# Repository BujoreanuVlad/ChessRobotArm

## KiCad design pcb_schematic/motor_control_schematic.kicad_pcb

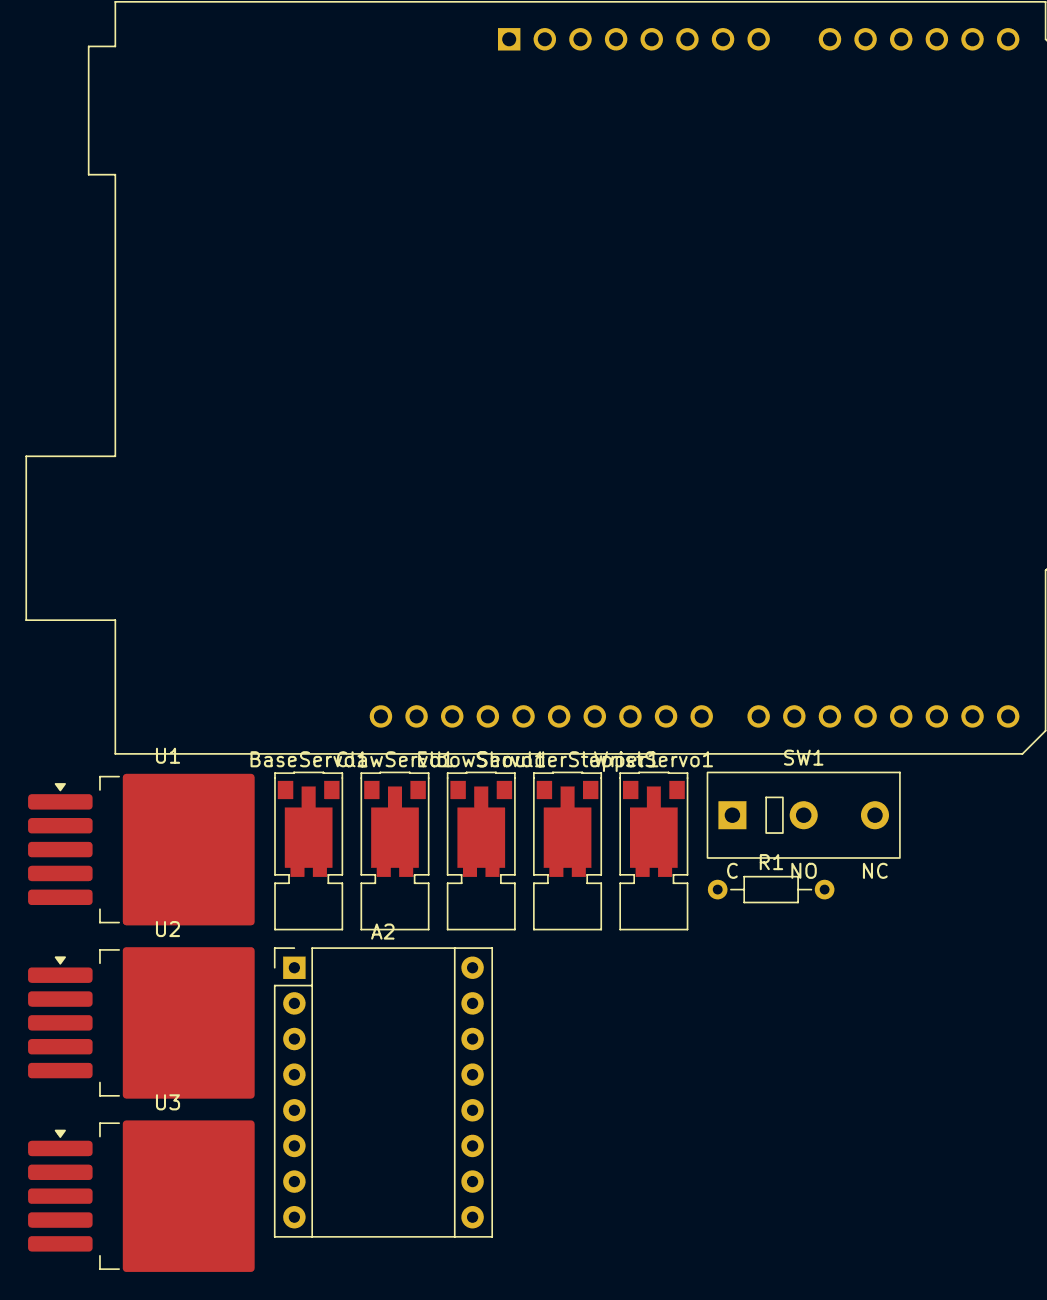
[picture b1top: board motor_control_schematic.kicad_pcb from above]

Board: 2 copper layers, 12 parts (0 on the bottom side), 15 nets, no tracks yet.

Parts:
A1: Arduino_UNO_R3
A2: Pololu_Breakout_DRV8825; Pololu_Breakout-16_15.2x20.3mm
BaseServo1: Motor_Servo; Vybronics_VZ30C1T8219732L
ClawServo1: Motor_Servo; Vybronics_VZ30C1T8219732L
ElbowServo1: Motor_Servo; Vybronics_VZ30C1T8219732L
R1: 10K; R_Axial_DIN0204_L3.6mm_D1.6mm_P7.62mm_Horizontal
SW1: SW_Push; SW_XKB_DM1-16UP-1
ShoulderStepper1: Stepper_Motor_bipolar; Vybronics_VZ30C1T8219732L
U1: XL4015; TO-263-5_TabPin3
U2, U3: LM2596S-ADJ; TO-263-5_TabPin3
WristServo1: Motor_Servo; Vybronics_VZ30C1T8219732L

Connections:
+12V: A2.8 (VMOT), U1.5 (VIN), U3.1 (VIN)
GND1: A2.7 (GND), U1.1 (GND), U2.3 (GND), U3.3 (GND)
unnamed: A1.5 (+5V), A2.13 (~RST), A2.14 (~SLP), SW1.1
unnamed: A1.17 (D2), A2.16 (DIR)
unnamed: A1.18 (D3), A2.15 (STEP)
unnamed: A1.19 (D4), R1.2, SW1.2
unnamed: A1.20 (D5), ClawServo1.1 (PWM)
unnamed: A1.21 (D6), WristServo1.1 (PWM)
unnamed: A1.24 (D9), ElbowServo1.1 (PWM)
unnamed: A1.25 (D10), BaseServo1.1 (PWM)
unnamed: A1.6 (GND), A2.1 (GND), R1.1
unnamed: A2.4 (A1), ShoulderStepper1.2 (-)
unnamed: A2.3 (A2), ShoulderStepper1.1
unnamed: BaseServo1.2 (+), ClawServo1.2 (+), U3.2 (OUT), WristServo1.2 (+)
unnamed: ElbowServo1.2 (+), U1.3 (SW), U2.1 (VIN)

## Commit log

2023-11-18 First prototype
2023-11-20 Added inertia
2023-12-22 Added a launch file and modified values to be more realistic
2024-02-09 Previous meshes for the robot
2024-02-10 First version of the stepper holder
2024-02-10 Added hole in the center for axle and fixed dimensions
2024-02-10 Fixed some distances
    Distance of the screws used to fix stepper in place shouldn't take into account the extra 5% padding of the piece
2024-02-12 Gear mounted on stepper
    Gear with a hole for the screw to better fix the gear to the stepper shaft
2024-02-14 Updated for 17HS13-0404S-PG27 motor
2024-02-14 Changes made for the 17HS13-0404S-PG27 motor
2024-02-14 Added adjustment due to difference between cylinder and base widths
2024-02-15 Shaft hole should be displaced by 1/2 of the difference, not by the whole difference
2024-02-16 22 teeth instead of 24
2024-02-17 Adapted holder for new motor
2024-02-17 First version of base gear
2024-02-17 Adjusted measurements
2024-02-17 Made gear bigger
2024-02-17 Fixed distances
2024-02-20 Made piece thicker so it opaque
2024-02-21 Tried with a smaller gear for greater torque
2024-02-21 Made gear bigger for greater torque
2024-02-23 Added gitignore
2024-02-26 First version of the first part of the arm
2024-03-02 Adjusted screw positions for part1 and built the link
2024-03-04 Finished part2 and combined link and part1
2024-03-05 Final version
2024-03-05 Increased height for part1 to compensate for link height
2024-03-05 Modified arm1 with sizes needed for arm2
2024-03-08 Added a hole for the nut
2024-03-08 Started working on board detection program
2024-03-10 Modified screw positions in part2
2024-03-24 First version of the poly gripper
2024-03-24 Padding for the current camera
2024-07-14 Sketch version of the code
2024-07-26 I forgor
2024-09-04 Made arm2 (forearm) smaller and lighter
2024-09-04 Python code to move arm through arduino
2024-09-20 Temp work
2024-10-20 Modified claw to be lighter
2024-10-20 Added project related datasheets
2024-10-20 Added documentation related files
2024-10-20 Added delay when moving servos
2024-11-02 Added variable to control servo speed
2024-11-03 Added support for shoulder control
2024-11-16 Made claws lighter
2024-11-22 Initial work
2024-12-13 Created round cut
2024-12-15 Finished clippers for holder and created servo gear
2024-12-20 Changed no of gear teeth to 33
2024-12-20 Started making changes for new arm combination
2024-12-27 Added holes to servo holder
2024-12-27 Re-made arm2 part1 design to function being turned by a gear
2024-12-27 Changed arm1 part2 design to be compatible with the new FT5335M servo
2024-12-31 Changed arm1-part2 for the 3 gear system
    The system currently uses an axle with 2 holes in it in order to secure the middle gear. This setup however snaps under the load of arm2 because of the weaknesses introduced by the holes
2024-12-31 Changed part2 to be compatible with new gear system
2024-12-31 Created axle holder
2025-01-10 Changed axle supporting gears
2025-01-10 Made servo holder thicker to not bend as much
2025-01-10 Changed arm1 to be compatible with the servo holder
2025-01-10 Added datasheet for elbow servo
2025-03-07 Modified arm1 part2 gear holes for new steel axles
2025-03-24 Changes for using a fixing screw for the servo
2025-03-25 Changed arm2-part1 to allow for more rotation freedom
2025-03-25 Made axle support thicker for arm1-part2
2025-03-26 Added code to update current shoulder angle position
2025-03-26 Made gripper holes larger to prevent the piece from breaking
2025-04-01 Fixed stepper controller
2025-04-01 Changed arm2-part1 to allow for more turning
2025-04-04 Refactored variables to use less space (converted them to 'byte' type) and wrote the function for inverse kinematics
2025-04-04 Created file for robot box
2025-04-04 Added function to convert angles to coords (forward kinematics), function to move robot vertically and added support for base servo motor
2025-04-18 Added more room for fitting on the robot
2025-04-18 Added holes for bottom panel nuts and power supply separator
2025-04-20 Finished robot box
2025-04-20 Created schematic file and added LEDs
2025-04-28 Changed servo speed and base motor lower and upper pulse width
2025-04-28 Made button holes larger and corrected switch position
2025-04-30 Renamed pcb_schematic to raspberry_schematic and created new schematic file for arduino and motor control
2025-05-01 Updated stl file
2025-05-01 Finished arduino motor controller schematic
2025-05-04 Added stepper calibration code
2025-05-05 Added vertical movement command
2025-05-06 Added horizontal movement command
2025-05-06 Added board movement command
2025-05-06 Finished raspberry schematic
2025-05-07 Created abstract Player class
2025-05-07 Changed raspberry schematic to use currently available resistors
2025-05-11 Found 2 more 15 ohm resistors to use instead of 2 10 ohm resistors
2025-05-11 Repaired mistaken gnd connection
2025-05-12 Robot state draft
2025-05-15 Added option to set LEDs in robotState
2025-05-15 Added arduino controller on raspberry side
2025-05-15 Added board move functionality in arduino
2025-05-16 Added function to get current state of led in robotState
2025-05-16 Added more base robot functions in main
2025-05-16 Fixed bugs in robotState
2025-05-16 Changed delay in arduino calibrate function
2025-05-16 Chadrv8825.h import in arduino sketch
2025-05-16 Changed main.py to contain hardcoded values for a chessboard
2025-05-16 Changed move horizontal arduino function
2025-05-16 Fixed arduino horizontal movement angle calculation
2025-05-18 More bug fixes for arduino horizontal movement
2025-05-19 Solved issue with too small buffer
2025-06-02 Fixed some bugs in horizontal movement and makeMove
2025-06-02 Changed default position of robot
2025-06-02 Fixed char to byte conversion bug
2025-06-02 Adder wrist error correction to moveVertical function
2025-06-02 Updated wrist error correction
2025-06-02 Updated wrist error correction to 15 deg
2025-06-02 Added new claw rest position
2025-06-02 Changed claw angles
2025-06-02 Switch move horizontal and vertical functions to use cosine interpolation
2025-06-03 Changed claw and arm lifting/lowering functions
2025-06-08 Modified chess player structure
2025-06-08 Changed robot state button actions registration to allow for multiple callbacks for same button
2025-06-19 Changes to Arduino code
2025-06-25 Separated chess board from game and added test cases for it
2025-07-01 Added chess engine
2025-07-08 Changed order of white and draw winner LED pins
2025-07-08 Added corner detection for board vision module
2025-07-12 Fixed identation issues in boardVision
2025-07-14 Improved warp function
2025-07-15 Implemented calibration code with corner detection
2025-07-15 Separated vision related code into a separate module
2025-07-15 Configured human player and modified test script
2025-07-15 Modified default positions in arduino code
2025-07-15 Bug fixes
2025-07-15 Changed piece recognizer model to mobilenetv2 for faster inference
2025-07-15 Fixed bugs with piece recognizer
2025-07-15 Changed piece recognizer to shufflenetv2 for even faster predictions
2025-07-15 Fixed some bugs in human player code
